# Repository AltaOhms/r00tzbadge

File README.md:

# r00tz badge 2016
Example code and eagle files for r00tz badge 2016

##To Solder the Badge
Under the [HookupGuide](https://github.com/HelloTechie/r00tzbadge/tree/master/HookupGuide) folder has the hook-up soldering guide.

##BOM - Bill of Materials

###[SparkFun](https://www.sparkfun.com)

* [SparkFun Redstick](https://www.sparkfun.com/products/13741)
* [LED Array](https://www.sparkfun.com/products/13795)
* [IR LED](https://www.sparkfun.com/products/9349)
* [4x Arduino Stackable Header - 6 pin](https://www.sparkfun.com/products/9280)
* [2x Momentary Pushbutton Switch - 12mm Square](https://www.sparkfun.com/products/9190)
* [BONUS: Thumb Joystick](https://www.sparkfun.com/products/9032)
* [BONUS: Joystick PCB](https://www.sparkfun.com/products/9110)

###[Pololu](https://www.pololu.com)

* [Battery Holder](https://www.pololu.com/product/1160)
* [Breakaway headers](https://www.pololu.com/product/965)

###[Digikey](http://www.digikey.com/) 

* [Standard Headers](http://www.digikey.com/product-detail/en/sullins-connector-solutions/PPTC121LFBN-RC/S6100-ND/807231)
* [IC IR RCVR MOD 38KHZ DOME RADIAL](http://www.digikey.com/scripts/DkSearch/dksus.dll?Detail&itemSeq=201968569&uq=636052976367495774)
* [56 Resistor](http://www.digikey.com/product-detail/en/stackpole-electronics-inc/CFM12JT56R0/S56HCT-ND/2617631)
* [330 ohm Resistor](http://www.digikey.com/product-detail/en/yageo/CFR-12JB-52-330R/330EBK-ND/4009)
* [ESD Bags](http://www.digikey.com/product-detail/en/scs/10046/SCP313-ND/1621588)

###Coding time!

####Redstick - An Arduino in a small form factor!
The Redstick [guide](https://learn.sparkfun.com/tutorials/redstick-hookup-guide?_ga=1.155838777.304927311.1426541708) is jammed packed with infomation on pin outs and how to get started coding!

If you are using Windows, you will need to install [FTDI Drivers](https://learn.sparkfun.com/tutorials/how-to-install-ftdi-drivers). 

####Arduino IDE
You will need to download the [Arduino IDE here](https://www.arduino.cc/en/Main/Software). Arduino is completely free and open source! What is great about the Arduino is that the community is huge and there is tons of example code and guides to help jump start your own projects. Included in this repo is [r00tz example code and libraries](https://github.com/HelloTechie/r00tzbadge/tree/master/Libraries). To learn how to add the r00tz arduino libraries, please follow this [tutorial](https://learn.sparkfun.com/tutorials/installing-an-arduino-library?_ga=1.197370157.304927311.1426541708).

Happy hacking!

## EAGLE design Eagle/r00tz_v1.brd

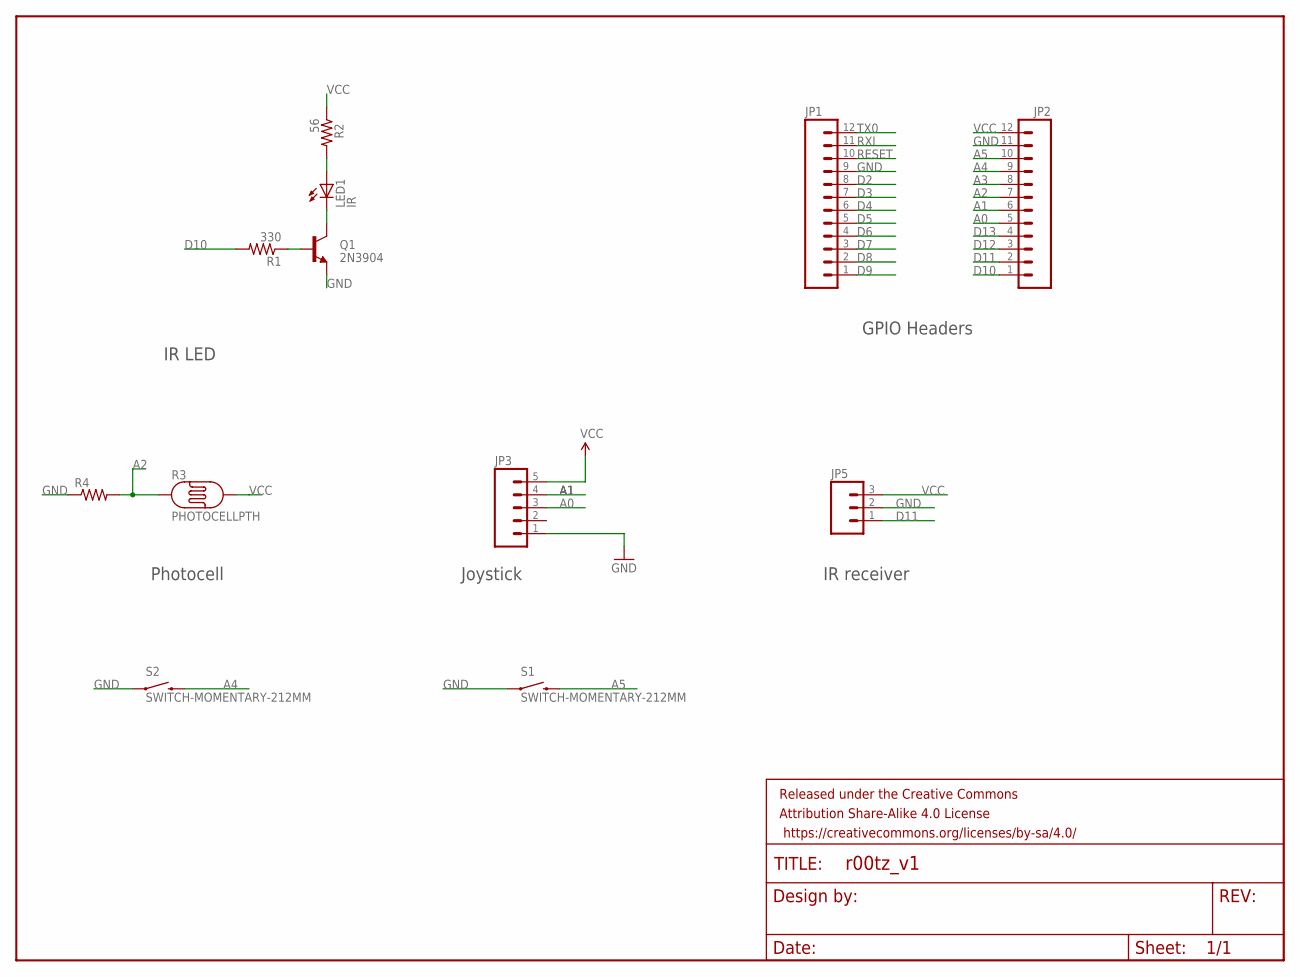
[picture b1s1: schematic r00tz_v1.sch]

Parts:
FRAME1: FRAME-LETTER; CREATIVE_COMMONS
JP1, JP2: M12PTH; 1X12
JP3: M05PTH; 1X05
JP5: M03PTH; 1X03
LED1: IR; LED5MM
Q1: 2N3904; TO-92
R1: 330; AXIAL-0.3
R2: 56; AXIAL-0.3
R3: PHOTOCELLPTH; PHOTOCELL
R4: 10KOHM-1/6W-5%(PTH)KIT; AXIAL-0.3-KIT
S1, S2: SWITCH-MOMENTARY-212MM; TACTILE-PTH-12MM

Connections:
A0: JP2.5, JP3.3
A1: JP2.6, JP3.4
A2: JP2.7, R3.1, R4.P$2 (2)
A3: JP2.8
A4: JP2.9, S2.3 (2)
A5: JP2.10, S1.3 (2)
D2: JP1.8
D3: JP1.7
D4: JP1.6
D5: JP1.5
D6: JP1.4
D7: JP1.3
D8: JP1.2
D9: JP1.1
D10: JP2.1, R1.P$2 (2)
D11: JP2.2, JP5.1
D12: JP2.3
D13: JP2.4
GND: JP1.9, JP2.11, JP3.1, JP5.2, Q1.1 (E), R4.P$1 (1), S1.1, S2.1
unnamed: LED1.K (C), Q1.3 (C)
unnamed: Q1.2 (B), R1.P$1 (1)
unnamed: LED1.A, R2.P$2 (2)
RESET: JP1.10
RXI: JP1.11
TX0: JP1.12
VCC: JP2.12, JP3.5, JP5.3, R2.P$1 (1), R3.2

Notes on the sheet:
GPIO Headers
Joystick
Photocell
IR LED
IR receiver

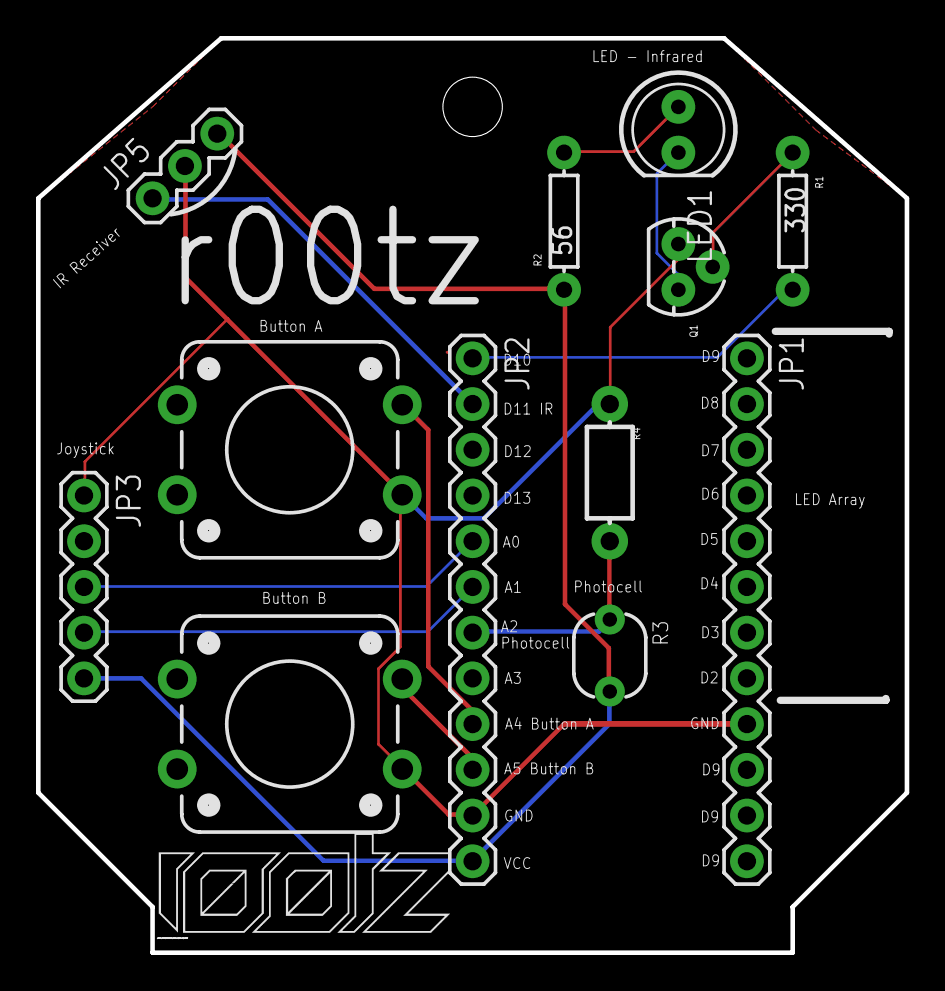
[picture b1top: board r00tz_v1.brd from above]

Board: 2 copper layers, 48.3 x 50.8 mm, 14 parts (0 on the bottom side), 12 nets.

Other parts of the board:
U$1: STAND-OFF

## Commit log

2016-08-05 Example libraries
    LED array and IR
2016-08-05 Eagle files
    Board layout
2016-08-05 Redstick link
2016-08-05 Photocell
    Photocell example
2016-08-06 Hookup Guide
    How to solder badge
2016-08-20 Soldering Badge Images
    Extra images for the soldering guide and where to stack the shield &
    Led Array on top of the Redstick
2016-08-20 Hookup Notes
2016-08-20 Additional Hookup Tips
2016-08-20 How to Get Started
    More info on how to get started

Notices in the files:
parts and their libraries:
SparkFun-Aesthetics: Licensing: Creative Commons ShareAlike 4.0 International - https://creativecommons.org/licenses/by-sa/4.0
SparkFun-Aesthetics: Released under the Creative Commons Attribution Share-Alike 4.0 License
SparkFun-Aesthetics: https://creativecommons.org/licenses/by-sa/4.0
